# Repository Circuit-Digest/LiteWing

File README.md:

## LiteWing

LiteWing is a compact, WiFi-controlled drone based on the ESP32-S3 microcontroller. Designed for hobbyists, makers, and engineers, LiteWing offers a simple yet powerful platform for drone experimentation and development. It is an open-hardware project, making it easy to modify and expand. Whether you're new to drones or an experienced developer looking to create custom flight applications, LiteWing provides an accessible and affordable way to explore drone technology. Unlike traditional drones that require proprietary controllers, LiteWing connects to your smartphone, allowing for an intuitive flying experience without additional hardware.

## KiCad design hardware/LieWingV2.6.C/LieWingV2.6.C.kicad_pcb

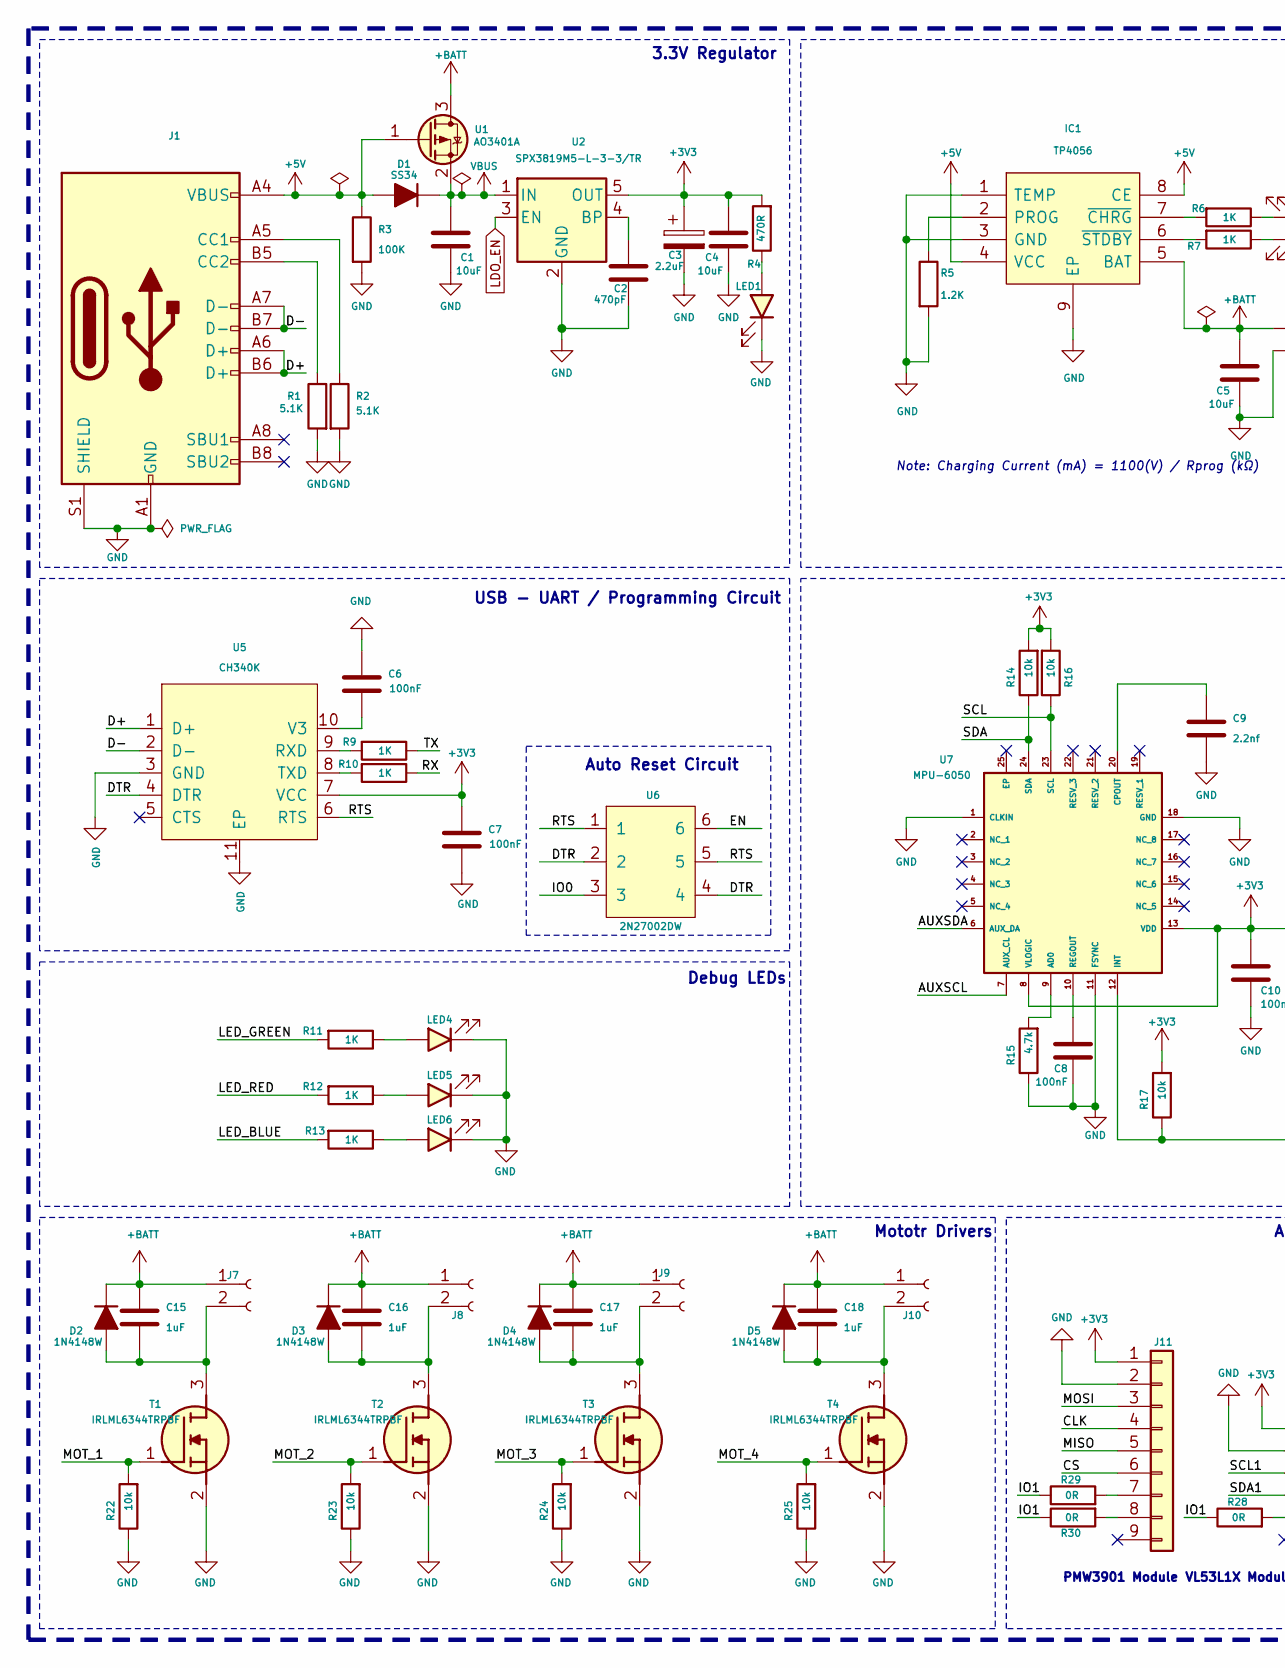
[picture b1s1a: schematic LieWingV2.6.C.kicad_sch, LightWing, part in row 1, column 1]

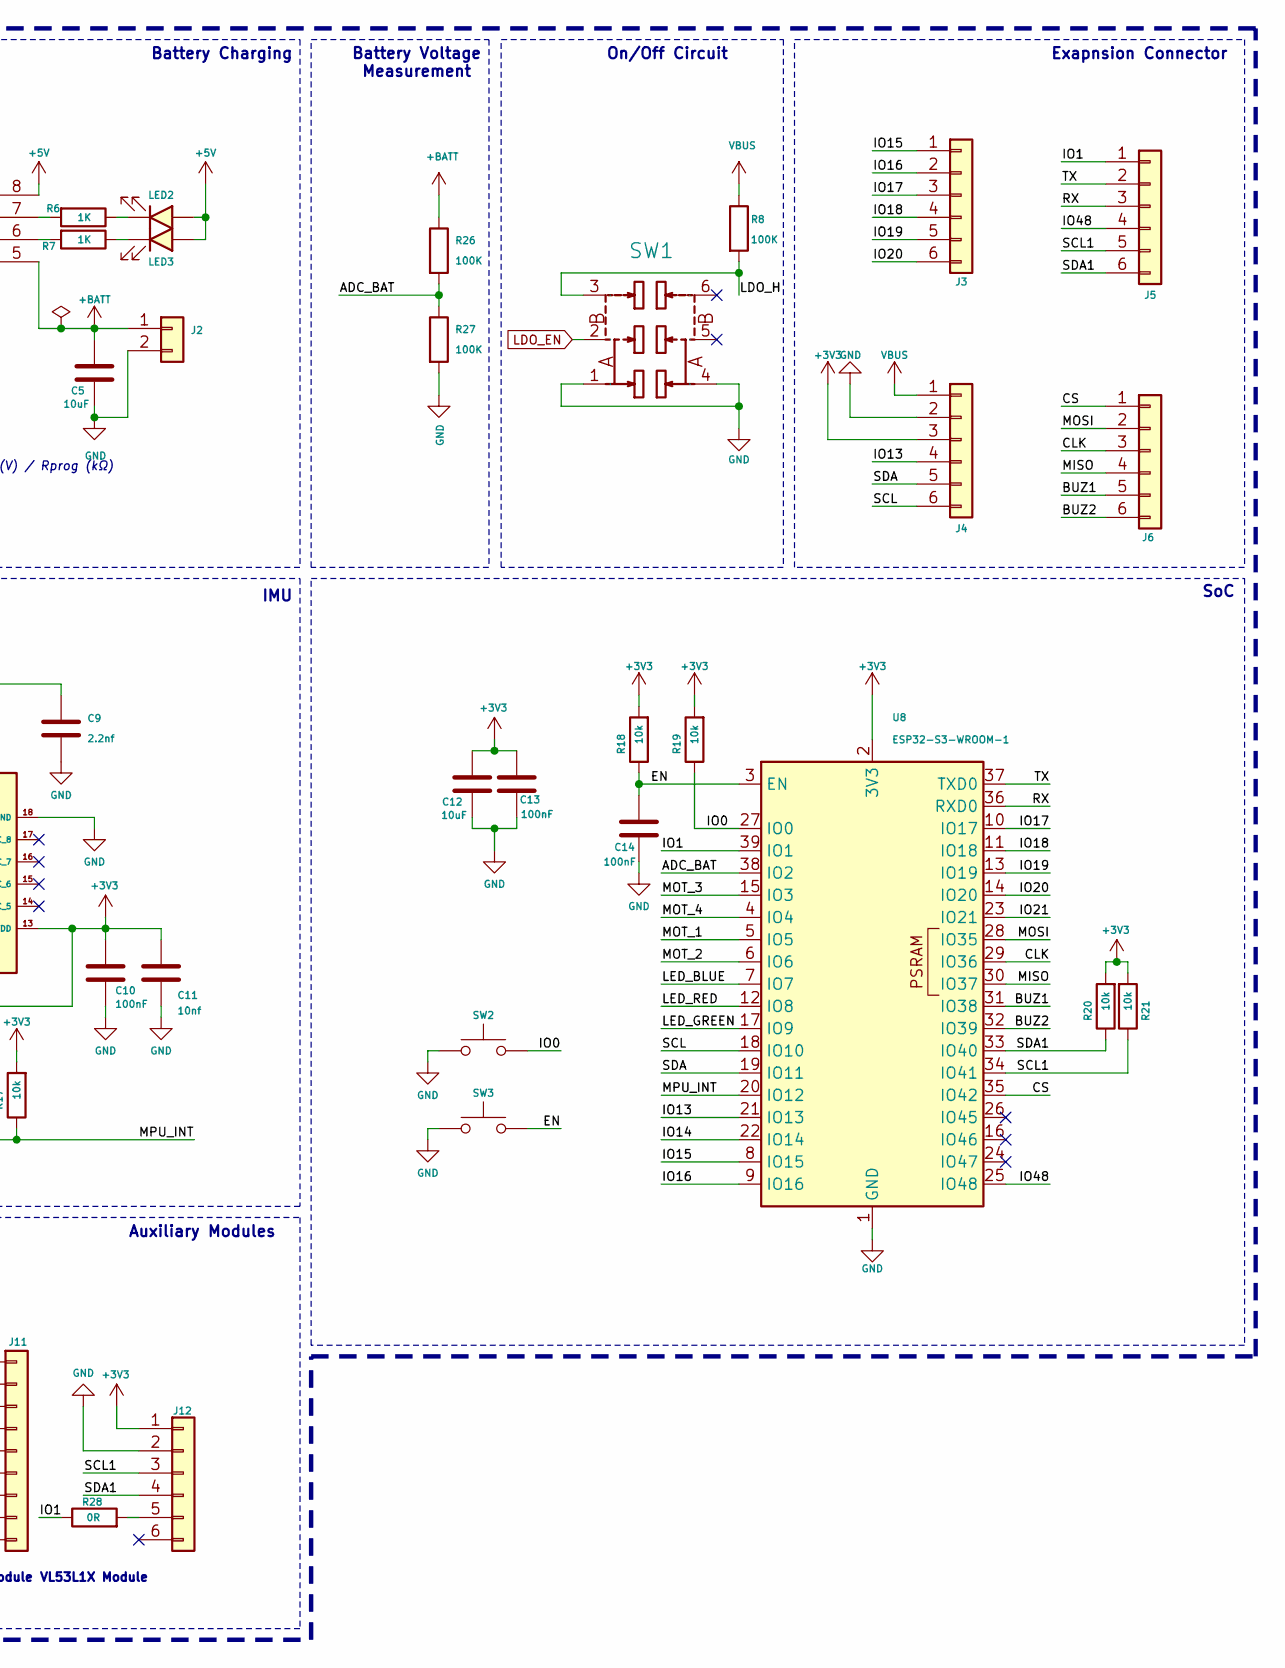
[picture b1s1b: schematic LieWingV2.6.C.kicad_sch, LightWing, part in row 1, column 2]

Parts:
C1, C4, C5, C12: 10uF; C_0603_1608Metric; MFR.Part # CL10A106KP8NNNC; LCSC Part # C19702
C2: 470pF; C_0603_1608Metric; MFR.Part # 0603B471K500NT; LCSC Part # C1620
C3: 2.2uF; C_0805_2012Metric; MFR.Part # TCC0805X7R225M250FT; LCSC Part # C5448893
C6, C7, C8, C10, C13, C14: 100nF; C_0603_1608Metric; MFR.Part # CC0603KRX7R9BB104; LCSC Part # C14663
C9: 2.2nf; C_0603_1608Metric; MFR.Part # 0603B222K500NT; LCSC Part # C1604
C11: 10nf; C_0603_1608Metric; MFR.Part # 0603B103K500NT; LCSC Part # C57112
C15, C16, C17, C18: 1uF; C_0603_1608Metric; MFR.Part # CL10A105KB8NNNC; LCSC Part # C15849
D1: SS34; D_SMA; MFR.Part # SS34; LCSC Part # C8678
D2, D3, D4, D5: 1N4148W; D_SOD-123F; MFR.Part # 1N4148W; LCSC Part # C81598
IC1: TP4056; SOIC127P600X175-9N; MFR.Part # TP4056; LCSC Part # C20199357
J1: USB_C_Receptacle_USB2.0; USB_C_Receptacle_HRO_TYPE-C-31-M-12; MFR.Part # USB-TYPE-C-018; LCSC Part # C2927038
J2: JST XH 2P 2.50mm SMD Hoz; CONN-TH_2P-P2.50_XH-2AW; MFR.Part # XH-2AW; LCSC Part # C33132
J3, J4, J5, J6: Conn_01x06; PinHeader_1x06_P2.54mm_Vertical
J7, J8, J9, J10: Conn_01x02_Female; LiteWingMotor2
J11: Conn_01x09; PMW3901
J12: Conn_01x06; VL53L1X_BREAKOUT
LED1, LED2, LED5: LED_Red; LED_0603_1608Metric; MFR.Part # KT-0603R; LCSC Part # C2286
LED3, LED6: LED_Blue; LED_0603_1608Metric; MFR.Part # KT-0603B; LCSC Part # C2288
LED4: LED_Green; LED_0603_1608Metric; MFR.Part # LTST-C193TGKT-5A; LCSC Part # C12065
R1, R2: 5.1K; R_0603_1608Metric; MFR.Part # 0603WAF5101T5E; LCSC Part # C23186
R3, R8, R26, R27: 100K; R_0603_1608Metric; MFR.Part # 0603WAF1003T5E; LCSC Part # C25803
R4: 470R; R_0603_1608Metric; MFR.Part # 0603WAF4700T5E; LCSC Part # C23179
R5: 1.2K; R_0603_1608Metric; MFR.Part # 0603WAF1201T5E; LCSC Part # C22765
R6, R7, R9, R10, R11, R12, R13: 1K; R_0603_1608Metric; MFR.Part # 0603WAF1001T5E; LCSC Part # C21190
R14, R16, R17, R18, R19, R20, R21, R22, R23, R24, R25: 10k; R_0603_1608Metric; MFR.Part # 0603WAF1002T5E; LCSC Part # C25804
R15: 4.7k; R_0603_1608Metric; MFR.Part # 0603WAF4701T5E; LCSC Part # C23162
R28, R29, R30: 0R; R_0603_1608Metric; MFR.Part # 0603WAF0000T5E; LCSC Part # C21189
SW1: MST22D18G2_125; SW-SMD_MST22D18G2; MFR.Part # MST22D18G2 125; LCSC Part # C2906280
SW2, SW3: Tactile Switch 3x4x2; Tactile 3x4x2mm TS-A010; MFR.Part # TS-KG88C-ART25F; LCSC Part # C2874433
T1, T2, T3, T4: IRLML6344TRPBF; SOT95P237X112-3N; MFR.Part # IRLML6344TRPBF-HXY; LCSC Part # C6285738
U1: AO3401A; SOT-23; MFR.Part # AO3401A; LCSC Part # C15127
U2: SPX3819M5-L-3-3/TR; SOT-23-5; MFR.Part # SPX3819M5-L-3-3/TR; LCSC Part # C9055
U5: CH340K; ESSOP-10_3.9x4.9mm_P1.00mm; MFR.Part # CH340K; LCSC Part # C18208922
U6: 2N27002DW; SOT-363_SC-70-6; MFR.Part # 2N27002DW; LCSC Part # C5190214
U7: MPU-6050; MPU6050; MFR.Part # MPU-6050; LCSC Part # C24112
U8: ESP32-S3-WROOM-1; MFR.Part # ESP32-S3-WROOM-1-N8; LCSC Part # C2913198

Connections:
+3V3: C3.1, C4.1, C7.1, C10.1, C11.1, C12.1, C13.1, J4.3, J11.1, J12.1, R4.2, R14.2, R16.2, R17.2, R18.2, R19.2, R20.2, R21.2, U2.5 (OUT), U5.7 (VCC), U7.8 (VLOGIC), U7.13 (VDD), U8.2 (3V3)
+5V: D1.2 (A), IC1.4 (VCC), IC1.8 (CE), J1.A4 (VBUS), J1.A9 (VBUS), J1.B4 (VBUS), J1.B9 (VBUS), LED2.2 (A), LED3.2 (A), R3.1, U1.1 (G)
+BATT: C5.1, C15.1, C16.1, C17.1, C18.1, D2.1 (K), D3.1 (K), D4.1 (K), D5.1 (K), IC1.5 (BAT), J2.1, J7.1, J8.1, J9.1, J10.1, R26.1, U1.3 (D)
/ADC_BAT: R26.2, R27.1, U8.38 (IO2)
/AUXSCL: U7.7 (AUX_CL)
/AUXSDA: U7.6 (AUX_DA)
/BUZ1: J6.5, U8.31 (IO38)
/BUZ2: J6.6, U8.32 (IO39)
/CLK: J6.3, J11.4, U8.29 (IO36)
/CS: J6.1, J11.6, U8.35 (IO42)
/D+: J1.A6 (D+), J1.B6 (D+), U5.1 (D+)
/D-: J1.A7 (D-), J1.B7 (D-), U5.2 (D-)
/DTR: U5.4 (DTR), U6.2, U6.4
/EN: C14.1, R18.1, SW3.2, U6.6, U8.3 (EN)
/IO0: R19.1, SW2.2, U6.3, U8.27 (IO0)
/IO1: J5.1, R28.1, R29.1, R30.1, U8.39 (IO1)
/IO13: J4.4, U8.21 (IO13)
/IO14: U8.22 (IO14)
/IO15: J3.1, U8.8 (IO15)
/IO16: J3.2, U8.9 (IO16)
/IO17: J3.3, U8.10 (IO17)
/IO18: J3.4, U8.11 (IO18)
/IO19: J3.5, U8.13 (IO19)
/IO20: J3.6, U8.14 (IO20)
/IO21: U8.23 (IO21)
/IO48: J5.4, U8.25 (IO48)
/LDO_H: R8.2, SW1.3
/LED_BLUE: R13.2, U8.7 (IO7)
/LED_GREEN: R11.2, U8.17 (IO9)
/LED_RED: R12.2, U8.12 (IO8)
/MISO: J6.4, J11.5, U8.30 (IO37)
/MOSI: J6.2, J11.3, U8.28 (IO35)
/MOT_1: R22.2, T1.1 (G), U8.5 (IO5)
/MOT_2: R23.2, T2.1 (G), U8.6 (IO6)
/MOT_3: R24.2, T3.1 (G), U8.15 (IO3)
/MOT_4: R25.2, T4.1 (G), U8.4 (IO4)
/MPU_INT: R17.1, U7.12 (INT), U8.20 (IO12)
/RTS: U5.6 (RTS), U6.1, U6.5
/RX: J5.3, R10.1, U8.36 (RXD0)
/SCL: J4.6, R16.1, U7.23 (SCL), U8.18 (IO10)
/SCL1: J5.5, J12.3, R21.1, U8.34 (IO41)
/SDA: J4.5, R14.1, U7.24 (SDA), U8.19 (IO11)
/SDA1: J5.6, J12.4, R20.1, U8.33 (IO40)
/TX: J5.2, R9.1, U8.37 (TXD0)
GND: C1.2, C2.2, C3.2, C4.2, C5.2, C6.1, C7.2, C8.2, C9.2, C10.2, C11.2, C12.2, C13.2, C14.2, IC1.1 (TEMP), IC1.3 (GND), IC1.9 (EP), J1.A1 (GND), J1.A12 (GND), J1.B1 (GND), J1.B12 (GND), J1.S1 (SHIELD), J2.2, J4.2, J11.2, J12.2, LED1.1 (K), LED4.1 (K), LED5.1 (K), LED6.1 (K), R1.2, R2.2, R3.2, R5.2, R15.1, R22.1, R23.1, R24.1, R25.1, R27.2, SW1.1, SW1.4, SW2.1, SW3.1, T1.2 (S), T2.2 (S), T3.2 (S), T4.2 (S), U2.2 (GND), U5.3 (GND), U5.11 (EP), U7.1 (CLKIN), U7.11 (FSYNC), U7.18 (GND), U8.1 (GND), U8.40 (GND), U8.41 (GND)
LDO_EN: SW1.2, U2.3 (EN)
unnamed: C15.2, D2.2 (A), J7.2, T1.3 (D)
unnamed: C16.2, D3.2 (A), J8.2, T2.3 (D)
unnamed: C17.2, D4.2 (A), J9.2, T3.3 (D)
unnamed: C18.2, D5.2 (A), J10.2, T4.3 (D)
unnamed: IC1.2 (PROG), R5.1
unnamed: IC1.7 (~CHRG), R6.2
unnamed: IC1.6 (~STDBY), R7.2
unnamed: J1.A5 (CC1), R2.1
unnamed: J1.B5 (CC2), R1.1
unnamed: J11.7, R29.2
unnamed: J11.8, R30.2
unnamed: J12.5, R28.2
unnamed: LED1.2 (A), R4.1
unnamed: LED2.1 (K), R6.1
unnamed: LED3.1 (K), R7.1
unnamed: LED4.2 (A), R11.1
unnamed: LED5.2 (A), R12.1
unnamed: LED6.2 (A), R13.1
unnamed: C2.1, U2.4 (BP)
unnamed: R9.2, U5.9 (RXD)
unnamed: R10.2, U5.8 (TXD)
unnamed: C6.2, U5.10 (V3)
unnamed: R15.2, U7.9 (AD0)
unnamed: C9.1, U7.20 (CPOUT)
unnamed: C8.1, U7.10 (REGOUT)
VBUS: C1.1, D1.1 (K), J4.1, R8.1, U1.2 (S), U2.1 (IN)

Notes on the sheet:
Note: Charging Current (mA) = 1100(V) / Rprog (kΩ)
IMU
VL53L1X Module
Debug LEDs
Battery Charging
3.3V Regulator
Battery Voltage Measurement
Auto Reset Circuit
USB - UART / Programming Circuit
SoC
Mototr Drivers
Exapnsion Connector
Auxiliary Modules
On/Off Circuit
PMW3901 Module

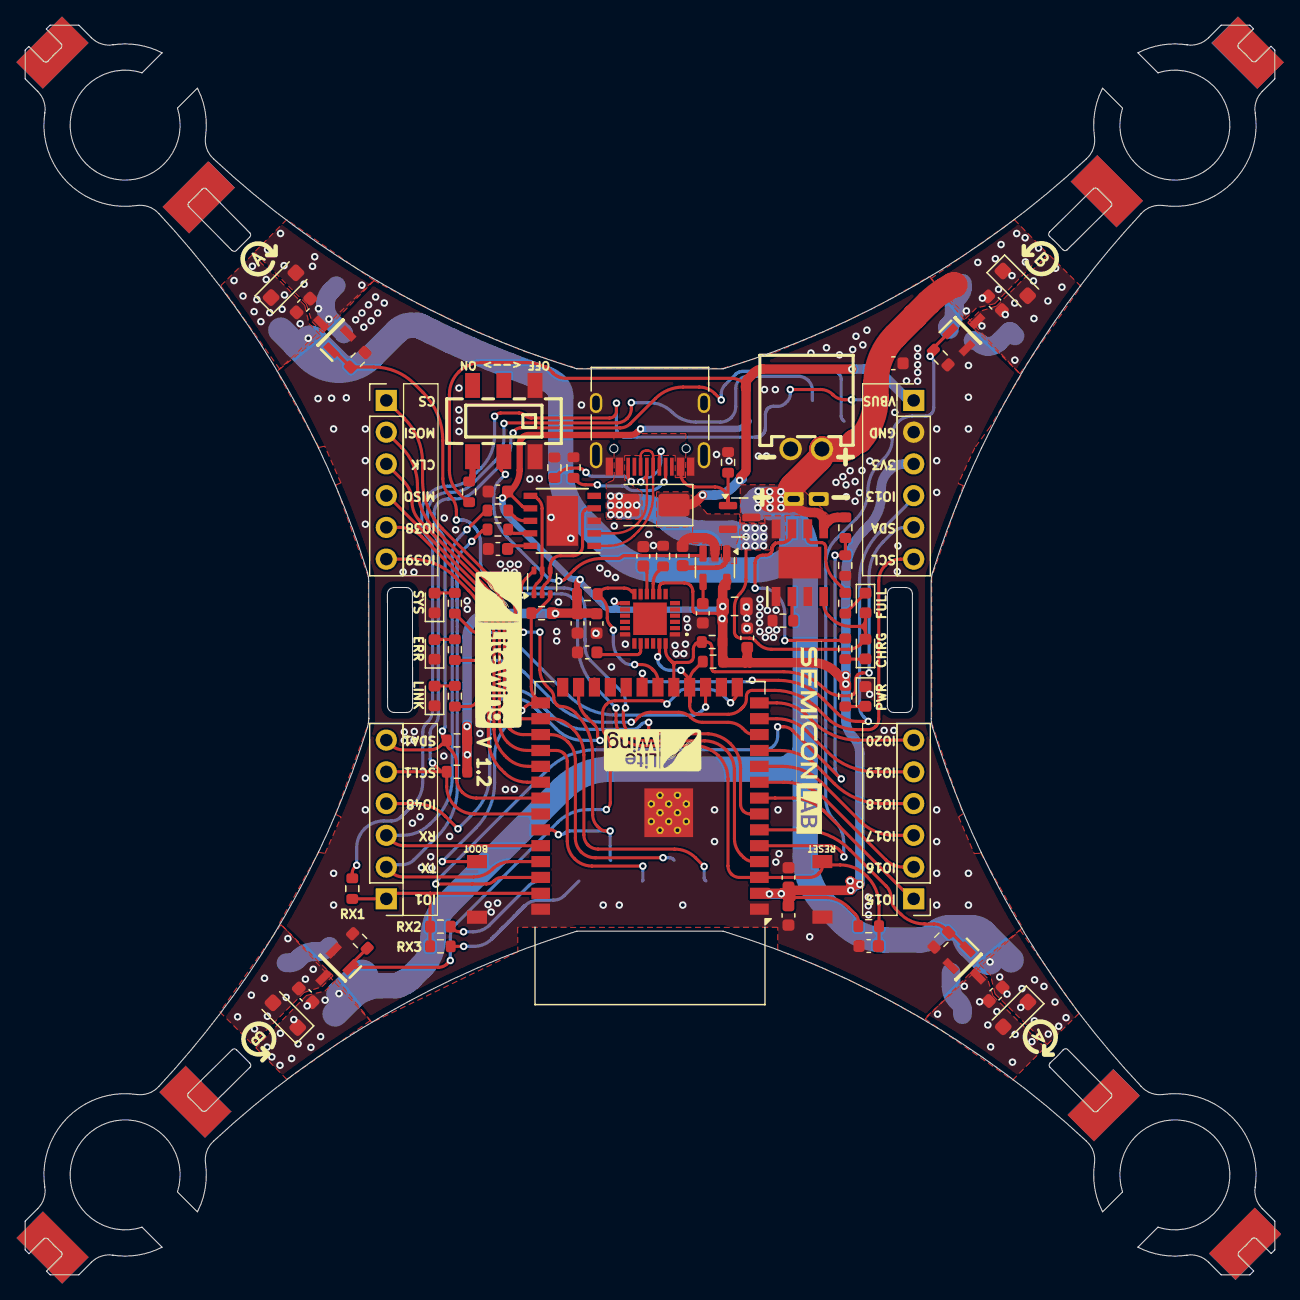
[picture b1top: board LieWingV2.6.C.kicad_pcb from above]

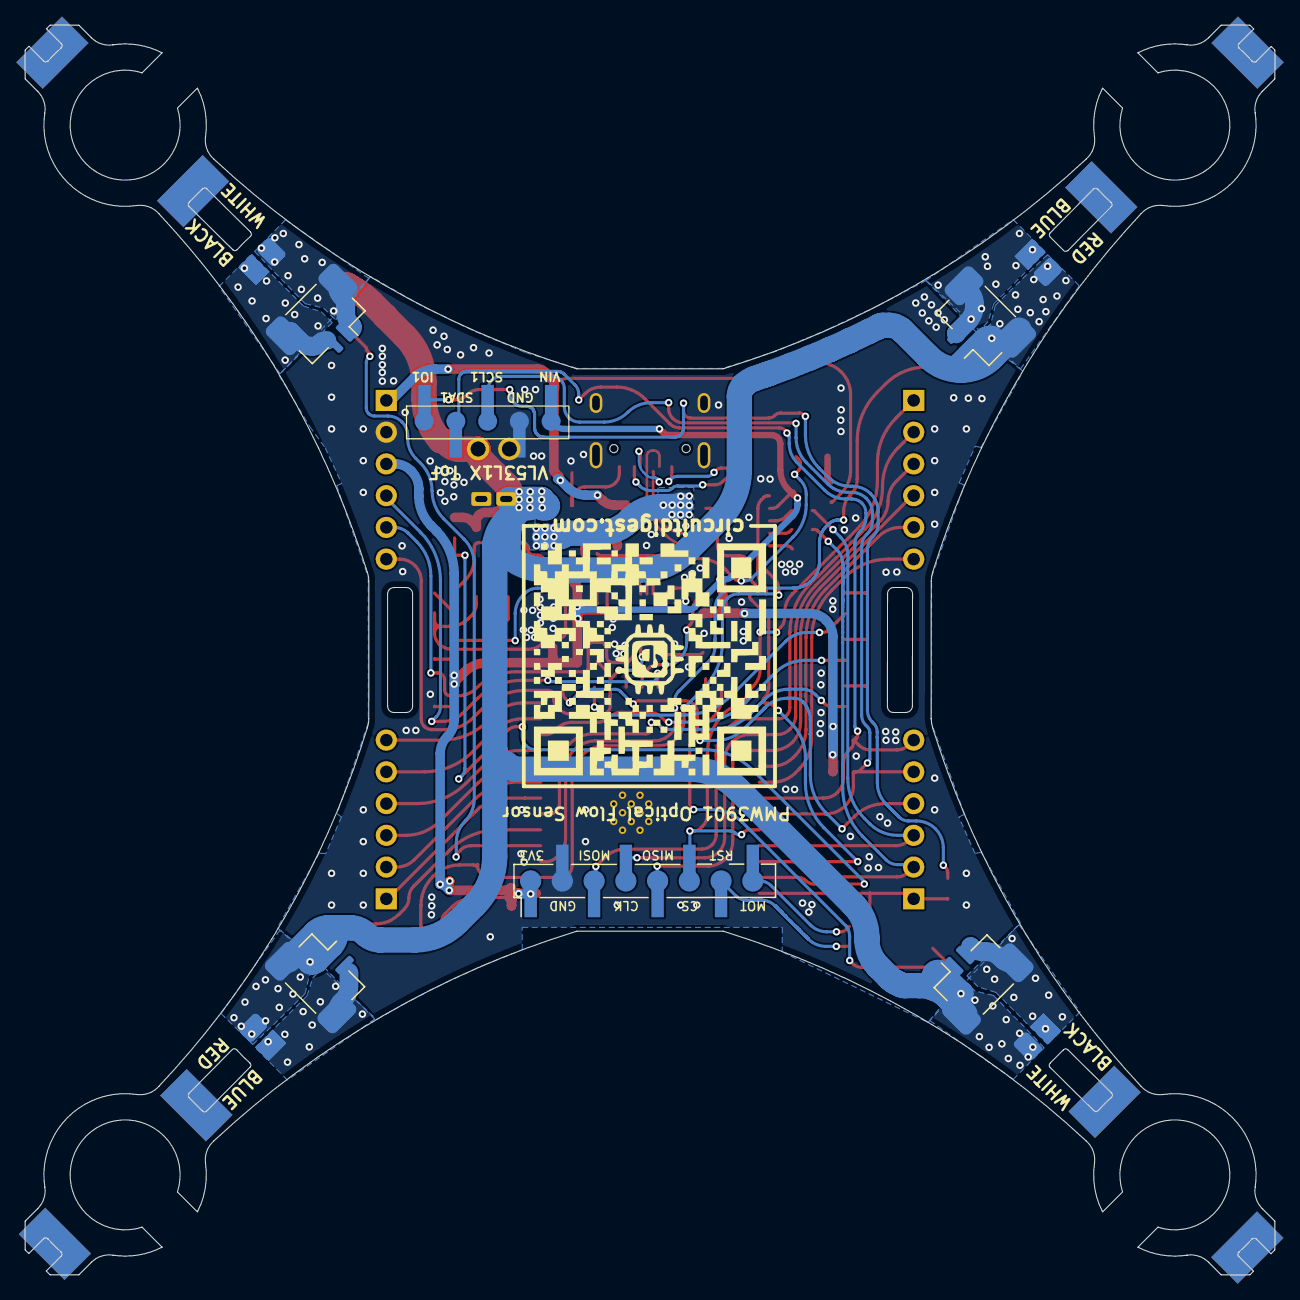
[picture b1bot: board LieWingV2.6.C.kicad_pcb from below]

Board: 2 copper layers, 100.0 x 100.0 mm, 85 parts (2 on the bottom side), 68 nets.

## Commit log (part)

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2025-07-21 Fixed spelling errors. Moved DroneV2 footprints into the repo instead of referencing the engineer's filesystem which lies outside of git source control.
2025-10-08 Python scripts for LightWing drone system
2025-10-08 Add Python scripts for Lightwing drone
2025-12-07 feat: add support for new Flight Stabilizer Module in LiteWing firmware
2025-12-15 Updated PCB to Version 2.6.C
2025-12-17 feat: Added Python Script for LiteWing Flight Stabilization Module
2025-12-17 refactor: clean up script implementation
2025-12-17 feat: add Python control script for LiteWing drone
2025-12-17 feat: add Python control script for LiteWing Flight Stabilization Module
2026-01-08 feat: Add Python script's for LiteWing Drone Flight Positioning Module Operations
2026-01-14 Updated Flight Positioning Module Firmware
2026-02-07 Rename hardware/LiteWing Drone Positioning ModuleV1.0.pdf to hardware/LiteWing Drone Positioning ModuleV1.0/LiteWing Drone Positioning ModuleV1.0.pdf
2026-02-07 Added Dead Reckoning Maneuvers Script
